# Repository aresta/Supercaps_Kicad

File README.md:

# Supercaps_Kicad
## Ultra low power device without batteries, zero maintenance, everlasting and environment friendly

Schema and PCB of the Supercaps project: https://github.com/aresta/Supercaps

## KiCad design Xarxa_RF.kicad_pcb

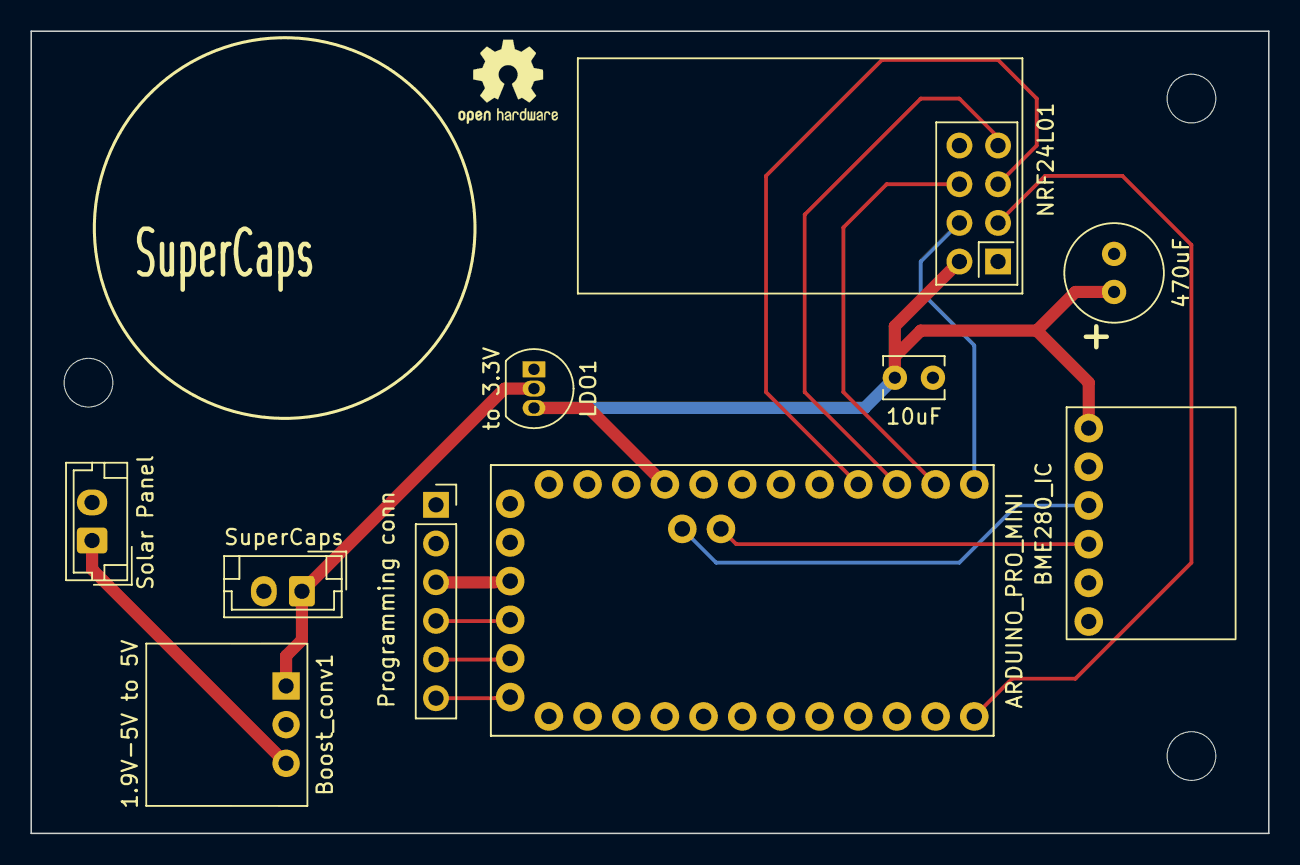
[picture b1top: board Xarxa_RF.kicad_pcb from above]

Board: 2 copper layers, 81.3 x 52.7 mm, 10 parts (0 on the bottom side), 15 nets.

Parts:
Boost_conv1: 1.9V-5V to 5V; Converter_DCDC_Murata_OKI-78SR_Horizontal
C1: 10uF; C_Disc_D3.8mm_W2.6mm_P2.50mm
C2: 470uF; C_Radial_D6.3mm_H11.0mm_P2.50mm
J1: Solar Panel; JST_EH_B2B-EH-A_1x02_P2.50mm_Vertical
J2: SuperCaps; JST_EH_B2B-EH-A_1x02_P2.50mm_Vertical
J5: Programming conn; PinSocket_1x06_P2.54mm_Vertical
LDO1: to 3.3V; TO-92_Inline
Sensor1: BME280_IC
U1: NRF24L01; nRF24L01_Breakout
U2: ARDUINO_PRO_MINI; MODULE_ARDUINO_PRO_MINI

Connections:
/DTR: J5.6, U2.JP1_1 (DTR)
/RX: J5.4, U2.JP1_3 (RXI)
/TX: J5.5, U2.JP1_2 (TXO)
/VCC: C1.1, C2.1, LDO1.3 (VO), Sensor1.1 (VCC), U1.2 (VCC), U2.JP1_4 (VCC)
/VCC1: J5.3, U2.JP6_4 (VCC_1)
GND: Boost_conv1.3 (GND), C1.2, C2.2, J1.2, J2.2, J5.1, J5.2, LDO1.1 (GND), Sensor1.2 (GND), U1.1 (GND), U2.JP1_5 (GND), U2.JP1_6 (GND)
unnamed: U1.3 (CE), U2.JP7_1 (D9)
unnamed: U1.4 (~CSN), U2.JP6_12 (D10)
unnamed: U1.5 (SCK), U2.JP6_9 (SCK)
unnamed: U1.6 (MOSI), U2.JP6_11 (MOSI)
unnamed: U1.7 (MISO), U2.JP6_10 (MISO)
unnamed: Sensor1.4 (SDA), U2.JP2_1 (A4)
unnamed: Sensor1.3 (SCL), U2.JP2_2 (A5)
Solar Panel: Boost_conv1.2 (SW), J1.1
SuperCap: Boost_conv1.1 (VOUT), J2.1, LDO1.2 (VI)

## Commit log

2023-01-28 Incial
